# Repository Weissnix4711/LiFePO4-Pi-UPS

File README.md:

# LiFePO4 Pi 4 UPS

Features:

- 1 LiFePO4 cell
- 500mA or 1.5A charge current
- USB C input, up to 3A
- DPM, but not DPPM
- I<sub>DPM</sub> = approx 3A
- 1x MAX17260 Fuel guage
- 1x INA219 current sensor for 5V output
- STM32F030x8 MCU

## KiCad project

See [Hardware/](Hardware/).

## Firmware

Todo

## Raspberry Pi auto-shutdown software

Todo

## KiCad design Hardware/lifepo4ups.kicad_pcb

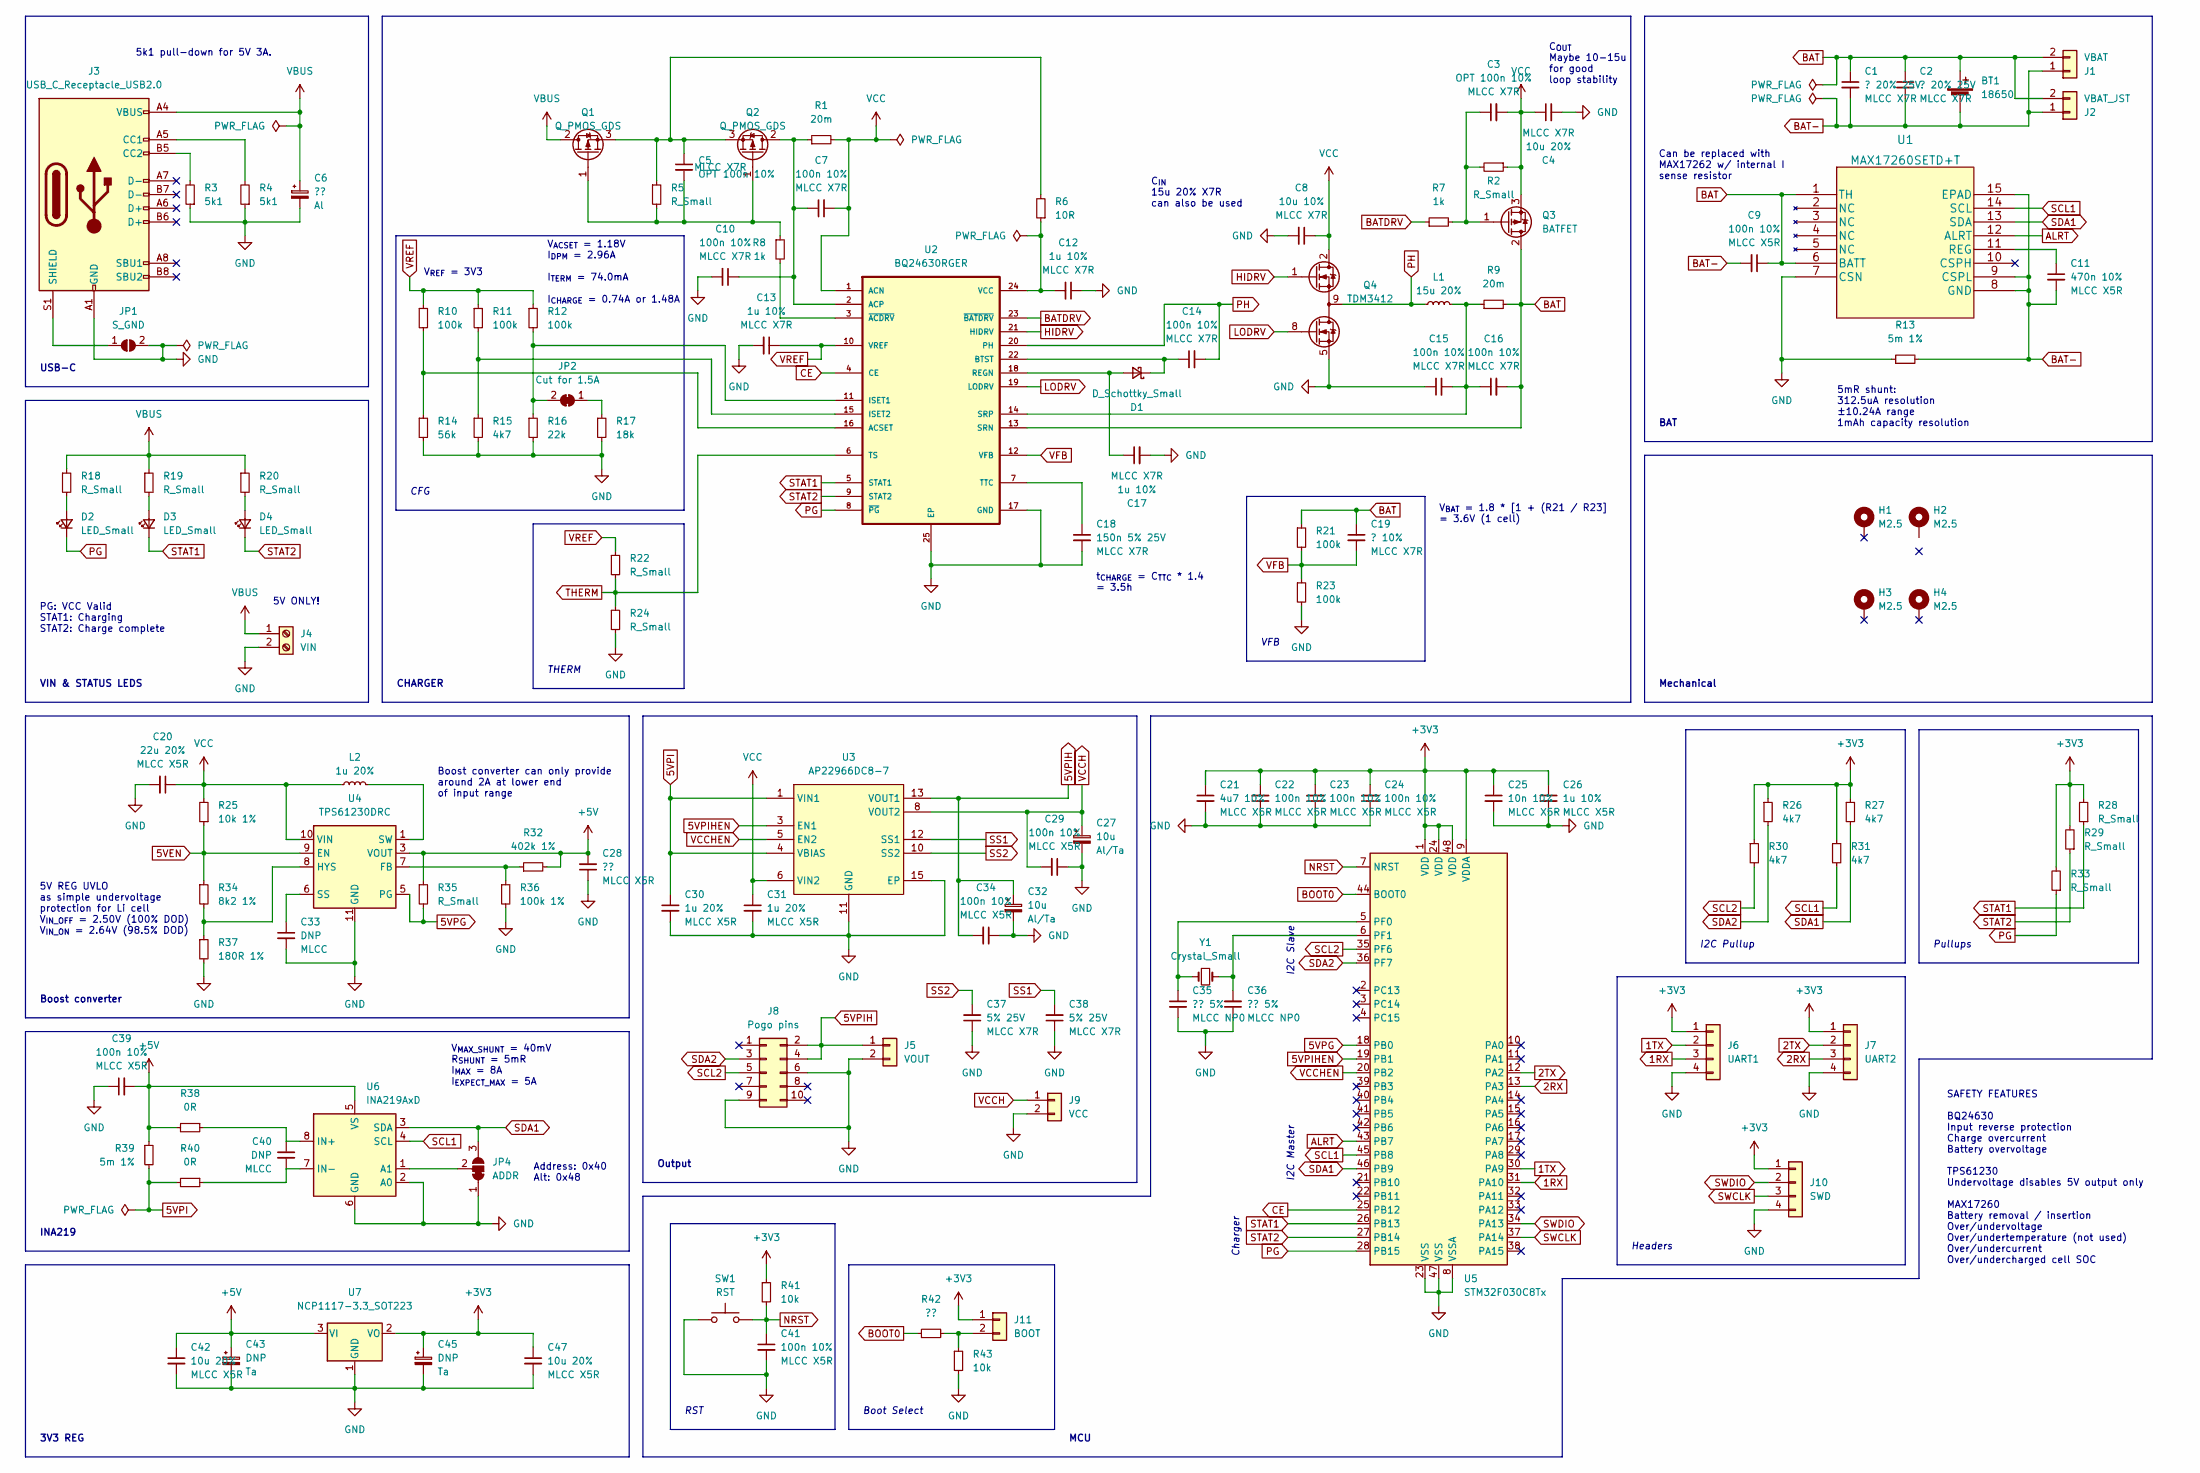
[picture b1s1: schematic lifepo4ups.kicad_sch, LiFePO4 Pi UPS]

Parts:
BT1: 18650; BatteryHolder_Keystone_1043_1x18650
C1, C2: ? 20% 25V; C_0805_2012Metric
C3, C5: OPT 100n 10%; C_0805_2012Metric
C4, C42, C47: 10u 20%; C_0805_2012Metric
C6: ??
C7, C9, C10, C14, C15, C16, C22, C23, C24, C29, C34, C39, C41: 100n 10%; C_0805_2012Metric
C8: 10u 10%; C_0805_2012Metric
C11: 470n 10%; C_0805_2012Metric
C12, C13, C17, C26: 1u 10%; C_0805_2012Metric
C18: 150n 5% 25V; C_0805_2012Metric
C19: ? 10%; C_0805_2012Metric
C20: 22u 20%; C_0805_2012Metric
C21: 4u7 10%; C_0805_2012Metric
C25: 10n 10%; C_0805_2012Metric
C27, C32: 10u
C28: ??; C_0805_2012Metric
C30, C31: 1u 20%; C_0805_2012Metric
C33, C40: DNP; C_0805_2012Metric
C35, C36: ?? 5%; C_0805_2012Metric
C37, C38: 5% 25V; C_0805_2012Metric
C43, C45: DNP; CP_EIA-2012-15_AVX-P
D1: D_Schottky_Small
D2, D3, D4: LED_Small; LED_0805_2012Metric
H1, H2, H3, H4: M2.5; MountingHole_2.7mm_M2.5_Pad
J1: VBAT; PinHeader_1x02_P2.54mm_Vertical
J2: VBAT_JST; JST_PH_S2B-PH-K_1x02_P2.00mm_Horizontal
J3: USB_C_Receptacle_USB2.0; USB_C_Receptacle_HRO_TYPE-C-31-M-12
J4: VIN; TerminalBlock_KF301-2P
J5: VOUT; PinHeader_1x02_P2.54mm_Vertical
J6: UART1; PinHeader_1x04_P2.54mm_Vertical
J7: UART2; PinHeader_1x04_P2.54mm_Vertical
J8: Pogo pins; PinHeader_2x05_P2.54mm_Vertical
J9: VCC; PinHeader_1x02_P2.54mm_Vertical
J10: SWD; PinHeader_1x04_P2.54mm_Horizontal
J11: BOOT; PinHeader_1x02_P2.54mm_Horizontal
JP1: S_GND; SolderJumper-2_P1.3mm_Open_RoundedPad1.0x1.5mm
JP2: Cut for 1.5A; SolderJumper-2_P1.3mm_Bridged_RoundedPad1.0x1.5mm
JP4: ADDR; SolderJumper-3_P1.3mm_Bridged12_RoundedPad1.0x1.5mm
L1: 15u 20%; L_1050
L2: 1u 20%; L_7030
Q1, Q2: Q_PMOS_GDS
Q3: BATFET; SOT-23
Q4: TDM3412; DFN3x3E-8_EP2_S
R1, R9: 20m; R_1206_3216Metric
R2, R5, R18, R19, R20, R22, R24, R28, R29, R33, R35: R_Small; R_0805_2012Metric
R3, R4: 5k1; R_0805_2012Metric
R6: 10R; R_0805_2012Metric
R7, R8: 1k; R_0805_2012Metric
R10, R11, R12, R21, R23: 100k; R_0805_2012Metric
R13, R39: 5m 1%; R_1206_3216Metric
R14: 56k; R_0805_2012Metric
R15, R26, R27, R30, R31: 4k7; R_0805_2012Metric
R16: 22k; R_0805_2012Metric
R17: 18k; R_0805_2012Metric
R25: 10k 1%; R_0805_2012Metric
R32: 402k 1%; R_0805_2012Metric
R34: 8k2 1%; R_0805_2012Metric
R36: 100k 1%; R_0805_2012Metric
R37: 180R 1%; R_0805_2012Metric
R38, R40: 0R; R_0805_2012Metric
R41, R43: 10k; R_0805_2012Metric
R42: ??; R_0805_2012Metric
SW1: RST; SW_Push_1P1T_NO_Vertical_Wuerth_434133025816
U1: MAX17260SETD+T; TDFN-14-1EP_3x3mm_P0.4mm_EP1.78x2.35mm
U2: BQ24630RGER; QFN50P400X400X100-25N
U3: AP22966DC8-7; V-DFN3020-14
U4: TPS61230DRC; Texas_S-PVSON-N10_ThermalVias
U5: STM32F030C8Tx; LQFP-48_7x7mm_P0.5mm
U6: INA219AxD; SOIC-8_3.9x4.9mm_P1.27mm
U7: NCP1117-3.3_SOT223; SOT-223-3_TabPin2
Y1: Crystal_Small; Crystal_SMD_HC49-SD

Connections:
1RX: J6.3, U5.31 (PA10)
1TX: J6.2, U5.30 (PA9)
2RX: J7.3, U5.13 (PA3)
2TX: J7.2, U5.12 (PA2)
5VEN: R25.1, R34.1, U4.9 (EN)
5VPG: R35.2, U4.5 (PG), U5.18 (PB0)
5VPI: C30.1, R39.2, R40.2, U3.1 (VIN1), U3.4 (VBIAS)
5VPIH: C32.1, C34.2, J5.1, J8.2, J8.4, U3.13 (VOUT1)
5VPIHEN: U3.3 (EN1), U5.19 (PB1)
+3V3: C21.1, C22.2, C23.2, C24.2, C25.1, C26.1, C45.1, C47.1, J6.1, J7.1, J10.1, J11.1, R26.1, R27.1, R28.2, R29.2, R30.1, R31.1, R33.2, R41.1, U5.1 (VDD), U5.9 (VDDA), U5.24 (VDD), U5.48 (VDD), U7.2 (VO)
+5V: C28.2, C39.2, C42.1, C43.1, R32.2, R35.1, R38.2, R39.1, U4.3 (VOUT), U4.4 (VOUT), U6.5 (VS), U7.3 (VI)
ALRT: U1.12 (ALRT), U5.43 (PB7)
BAT: BT1.1 (+), C1.1, C2.1, C9.1, C16.2, C19.1, J1.2, J2.2, Q3.2 (D), R9.2, R21.1, U1.1 (TH), U1.6 (BATT), U2.13 (SRN)
BAT-: BT1.2 (-), C1.2, C2.2, C9.2, C11.2, J1.1, J2.1, R13.2, U1.8 (GND), U1.9 (CSPL), U1.15 (EPAD)
BATDRV: R7.1, U2.23 (~BATDRV)
BOOT0: R42.1, U5.44 (BOOT0)
CE: U2.4 (CE), U5.25 (PB12)
GND: C4.2, C6.2, C8.2, C10.2, C12.1, C13.2, C15.1, C17.2, C18.2, C20.2, C21.2, C22.1, C23.1, C24.1, C25.2, C26.2, C27.2, C28.1, C29.1, C30.2, C31.2, C32.2, C33.2, C34.1, C35.2, C36.1, C37.1, C38.1, C39.1, C41.2, C42.2, C43.2, C45.2, C47.2, J3.A1 (GND), J3.A12 (GND), J3.B1 (GND), J3.B12 (GND), J4.2, J5.2, J6.4, J7.4, J8.6, J8.9, J9.2, J10.4, JP1.2 (B), JP4.1 (A), Q4.5 (S2), Q4.6 (S2), Q4.7 (S2), R3.1, R4.1, R13.1, R14.2, R15.2, R16.2, R17.2, R23.2, R24.2, R36.2, R37.2, R43.2, SW1.1, U1.7 (CSN), U2.17 (GND), U2.25 (EP), U3.11 (GND), U3.15 (EP), U4.11 (GND), U5.8 (VSSA), U5.23 (VSS), U5.47 (VSS), U6.2 (A0), U6.6 (GND), U7.1 (GND)
HIDRV: Q4.1 (G1), U2.21 (HIDRV)
LODRV: Q4.8 (G2), U2.19 (LODRV)
NRST: C41.1, R41.2, SW1.2, U5.7 (NRST)
unnamed: C3.1, Q3.1 (G), R2.2, R7.2
unnamed: C5.1, Q1.3 (S), Q2.3 (S), R5.1, R6.2
unnamed: C5.2, Q1.1 (G), Q2.1 (G), R5.2, R8.1
unnamed: C7.1, C10.1, Q2.2 (D), R1.1, U2.2 (ACP)
unnamed: C11.1, U1.11 (REG)
unnamed: C12.2, R6.1, U2.24 (VCC)
unnamed: C14.1, D1.1 (K), U2.22 (BTST)
unnamed: C15.2, C16.1, L1.2, R9.1, U2.14 (SRP)
unnamed: C17.1, D1.2 (A), U2.18 (REGN)
unnamed: C18.1, U2.7 (TTC)
unnamed: C33.1, U4.6 (SS)
unnamed: C35.1, U5.5 (PF0), Y1.2
unnamed: C36.2, U5.6 (PF1), Y1.1
unnamed: C40.1, R38.1, U6.8 (IN+)
unnamed: C40.2, R40.1, U6.7 (IN-)
unnamed: D2.2 (A), R18.2
unnamed: D3.2 (A), R19.2
unnamed: D4.2 (A), R20.2
unnamed: J3.A5 (CC1), R4.2
unnamed: J3.B5 (CC2), R3.2
unnamed: J3.S1 (SHIELD), JP1.1 (A)
unnamed: J11.2, R42.2, R43.1
unnamed: JP2.1 (A), R17.1
unnamed: JP2.2 (B), R12.2, R16.1, U2.11 (ISET1)
unnamed: JP4.2 (C), U6.1 (A1)
unnamed: L2.2, U4.1 (SW), U4.2 (SW)
unnamed: R8.2, U2.3 (~ACDRV)
unnamed: R10.2, R14.1, U2.16 (ACSET)
unnamed: R11.2, R15.1, U2.15 (ISET2)
unnamed: R32.1, R36.1, U4.7 (FB)
unnamed: R34.2, R37.1, U4.8 (HYS)
PG: D2.1 (K), R33.1, U2.8 (~PG), U5.28 (PB15)
PH: C14.2, L1.1, Q4.9 (S1/D2), U2.20 (PH)
SCL1: R31.2, U1.14 (SCL), U5.45 (PB8), U6.4 (SCL)
SCL2: J8.5, R30.2, U5.35 (PF6)
SDA1: JP4.3 (B), R27.2, U1.13 (SDA), U5.46 (PB9), U6.3 (SDA)
SDA2: J8.3, R26.2, U5.36 (PF7)
SS1: C38.2, U3.12 (SS1)
SS2: C37.2, U3.10 (SS2)
STAT1: D3.1 (K), R28.1, U2.5 (STAT1), U5.26 (PB13)
STAT2: D4.1 (K), R29.1, U2.9 (STAT2), U5.27 (PB14)
SWCLK: J10.3, U5.37 (PA14)
SWDIO: J10.2, U5.34 (PA13)
THERM: R22.2, R24.1, U2.6 (TS)
VBUS: C6.1, J3.A4 (VBUS), J3.A9 (VBUS), J3.B4 (VBUS), J3.B9 (VBUS), J4.1, Q1.2 (D), R18.1, R19.1, R20.1
VCC: C3.2, C4.1, C7.2, C8.1, C20.1, C31.1, L2.1, Q3.3 (S), Q4.2 (D1), Q4.3 (D1), Q4.4 (D1), R1.2, R2.1, R25.2, U2.1 (ACN), U3.6 (VIN2), U4.10 (VIN)
VCCH: C27.1, C29.2, J9.1, U3.8 (VOUT2)
VCCHEN: U3.5 (EN2), U5.20 (PB2)
VFB: C19.2, R21.2, R23.1, U2.12 (VFB)
VREF: C13.1, R10.1, R11.1, R12.1, R22.1, U2.10 (VREF)

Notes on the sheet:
5mR shunt: 312.5uA resolution ±10.24A range 1mAh capacity resolution
Can be replaced with MAX17262 w/ internal I sense resistor
INA219
VIN & STATUS LEDS
Charger
THERM
5k1 pull-down for 5V 3A.
Mechanical
Output
CHARGER
Boot Select
V_{ACSET} = 1.18V I_{DPM} = 2.96A I_{TERM} = 74.0mA I_{CHARGE} = 0.74A or 1.48A
5V ONLY!
MCU
Address: 0x40 Alt: 0x48
Boost converter can only provide around 2A at lower end of input range
Pullups
CFG
V_{REF} = 3V3
BAT
Headers
USB-C
V_{MAX_SHUNT} = 40mV R_{SHUNT} = 5mR I_{MAX} = 8A I_{EXPECT_MAX} = 5A
VFB
V_{BAT} = 1.8 * [1 + (R21 / R23] = 3.6V (1 cell)
t_{CHARGE} = C_{TTC} * 1.4 = 3.5h
RST
C_{OUT} Maybe 10-15u for good loop stability
3V3 REG
C_{IN} 15u 20% X7R can also be used
I2C Master
SAFETY FEATURES BQ24630 Input reverse protection Charge overcurrent Battery overvoltage TPS61230 Undervoltage disables 5V output only MAX17260 Battery removal / insertion Over/undervoltage Over/undertemperature (not used) Over/undercurrent Over/undercharged cell SOC
Boost converter
I2C Slave
I2C Pullup
5V REG UVLO as simple undervoltage protection for Li cell V_{IN_OFF} = 2.50V (100% DOD) V_{IN_ON} = 2.64V (98.5% DOD)
PG: VCC Valid STAT1: Charging STAT2: Charge complete

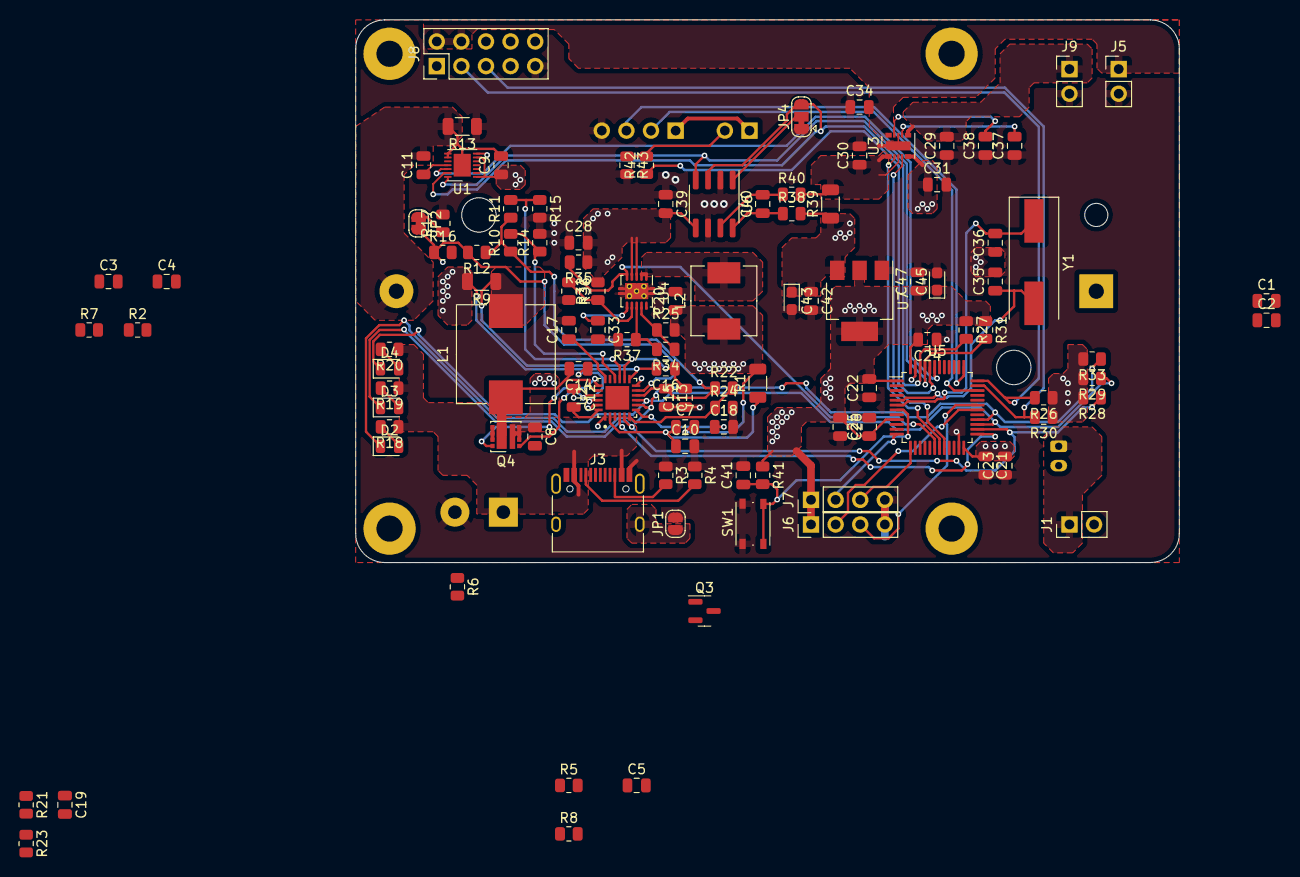
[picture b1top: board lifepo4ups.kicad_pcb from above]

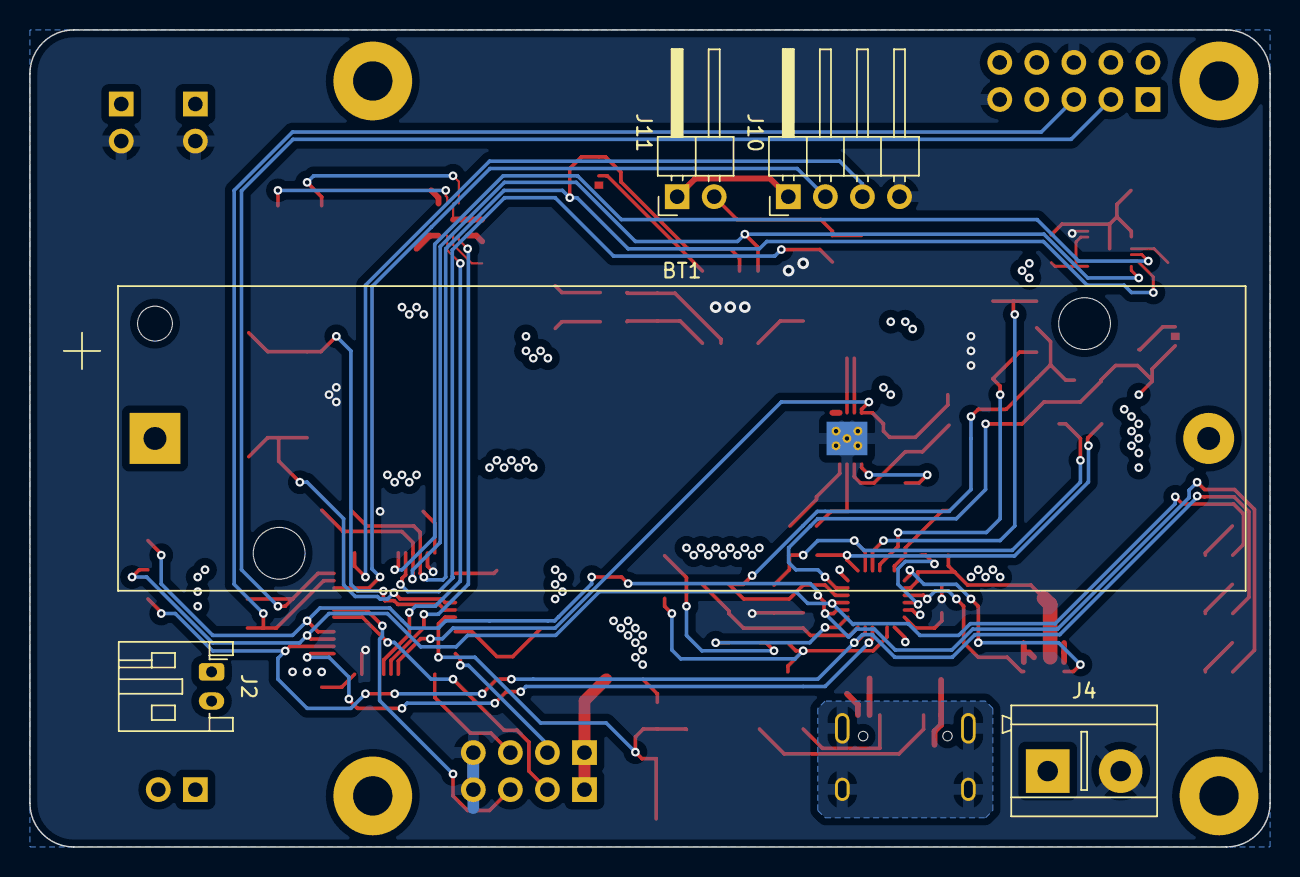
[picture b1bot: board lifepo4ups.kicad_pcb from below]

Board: 4 copper layers, 85.0 x 56.0 mm, 120 parts (5 on the bottom side), 71 nets.

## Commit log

2022-07-28 Fix README
2022-08-14 Update libraries
2022-08-14 Update schematic
2022-08-14 Start layout
